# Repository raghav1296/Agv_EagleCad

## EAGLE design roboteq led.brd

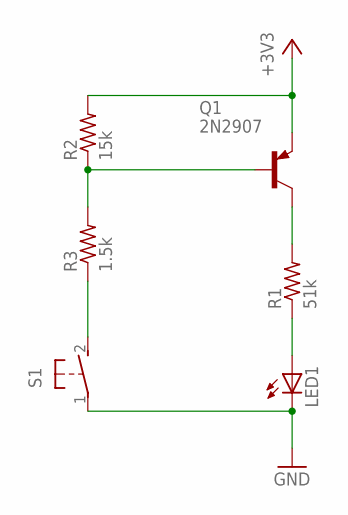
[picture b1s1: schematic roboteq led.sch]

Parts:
LED1: LED; SMARTLED-TTW
Q1: 2N2907; TO92-EBC-OVAL
R1: 51k; 0204V
R2: 15k; 0204V
R3: 1.5k; 0204V
S1: 31-XX; B3F-31XX

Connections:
+3V3: Q1.E, R2.2
GND: LED1.C@1 (C), S1.1
unnamed: Q1.C, R1.2
unnamed: LED1.A@1 (A), R1.1
unnamed: Q1.B, R2.1, R3.2
unnamed: R3.1, S1.2 (S)

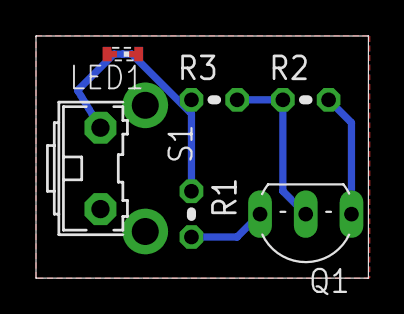
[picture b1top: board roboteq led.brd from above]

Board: 2 copper layers, 18.5 x 13.5 mm, 6 parts (0 on the bottom side), 6 nets.

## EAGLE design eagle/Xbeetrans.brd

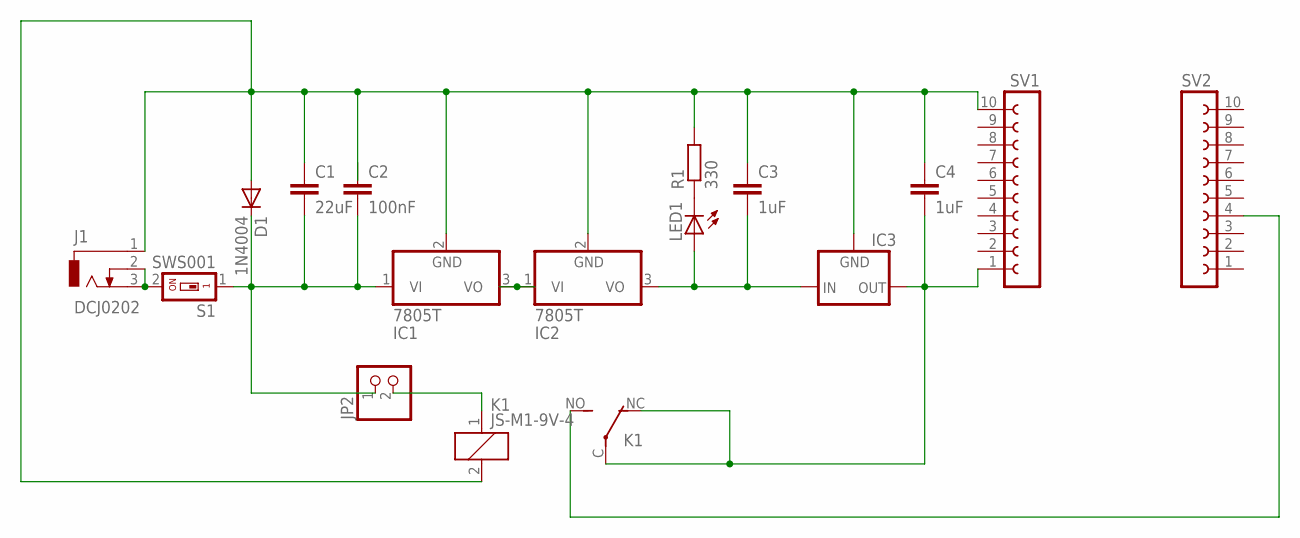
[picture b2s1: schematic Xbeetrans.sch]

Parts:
C1: 22uF; C025-025X050
C2: 100nF; C025-025X050
C3, C4: 1uF; C025-025X050
D1: 1N4004; DO41-10
IC1, IC2: 7805T; TO220H
IC3: MCP1700TRI; TO92
J1: DCJ0202
JP2: PINHD-1X2; 1X02
K1: JS-M1-9V-4; JS-M
LED1: LED3MM
R1: 330; 0204/5
S1: SWS001; SMS-001
SV1, SV2: FE10-1; FE10

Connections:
GND: C1.1, C2.1, C3.1, C4.1, D1.A, IC1.2 (GND), IC2.2 (GND), IC3.1 (GND), J1.1, K1.2, R1.2, SV1.10
unnamed: J1.2, J1.3, S1.2
unnamed: C1.2, C2.2, D1.C, IC1.1 (VI), JP2.1, S1.1
unnamed: JP2.2, K1.1
unnamed: LED1.K (C), R1.1
unnamed: C3.2, IC2.3 (VO), IC3.2 (IN), LED1.A
unnamed: IC1.3 (VO), IC2.1 (VI)
XBEE3.3: C4.2, IC3.3 (OUT), K1.C, K1.NC (O), SV1.1
XBEED: K1.NO (S), SV2.4

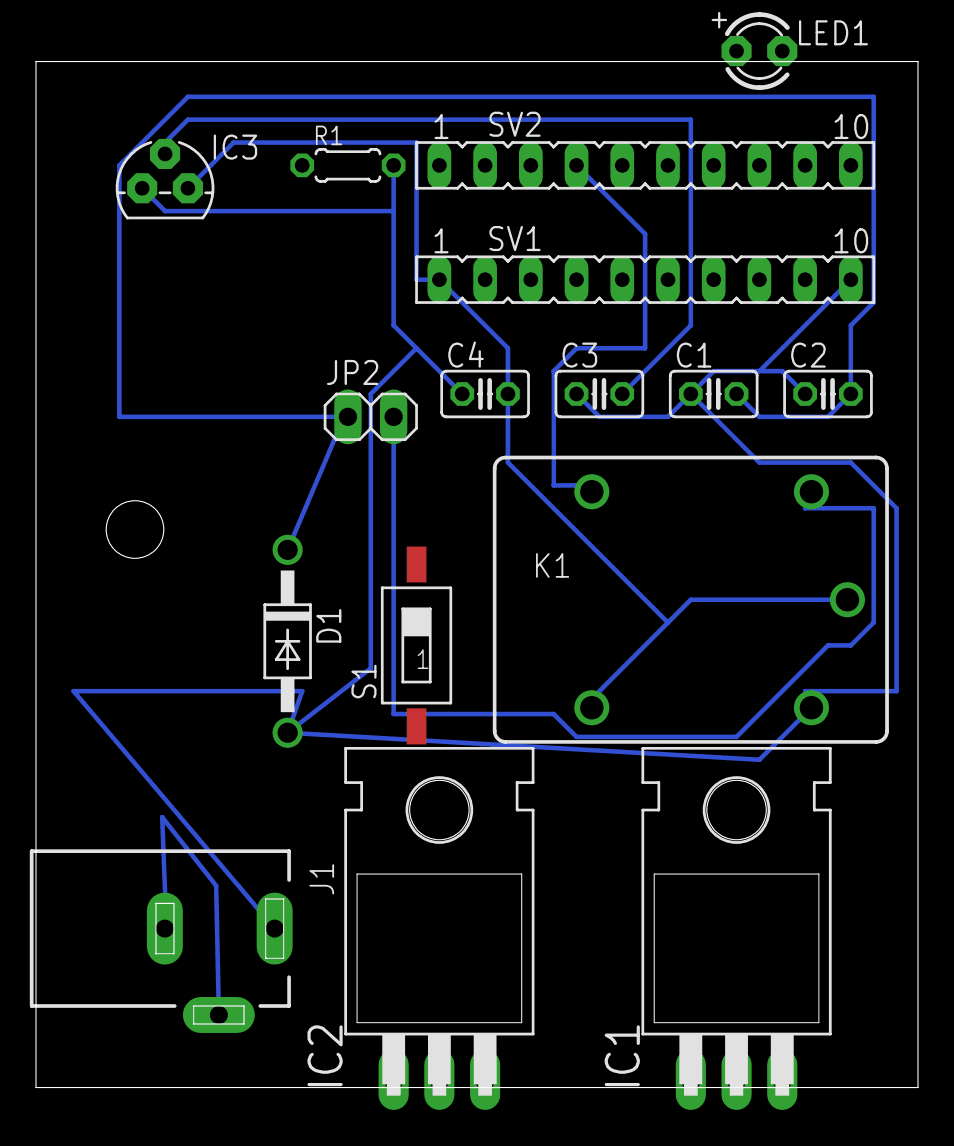
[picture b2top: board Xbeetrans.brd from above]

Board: 2 copper layers, 49.0 x 57.0 mm, 16 parts (0 on the bottom side), 9 nets.

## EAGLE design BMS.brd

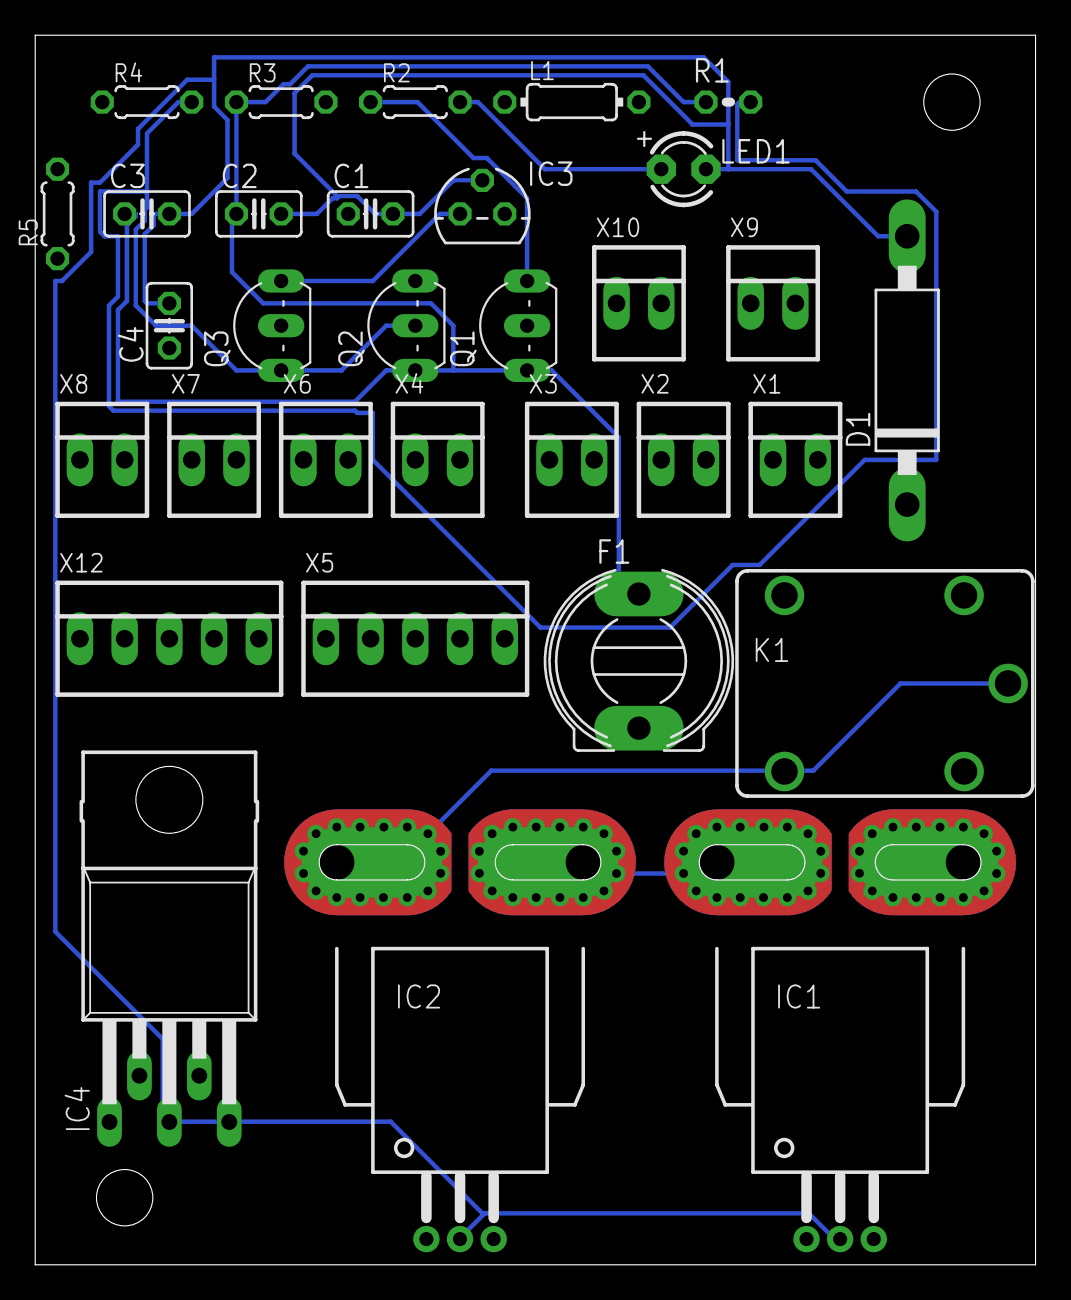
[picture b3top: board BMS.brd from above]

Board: 2 copper layers, 56.8 x 69.8 mm, 32 parts (0 on the bottom side), 13 nets.

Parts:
C1, C2, C3, C4: C025-025X050
D1: C1702-15
F1: KS9V
IC1, IC2: ACS750LCA-050; ACS75050
IC3: 78L08Z; TO92
IC4: TO220-52
K1: CQ1-12V; CQ1
L1: 0204/7
LED1: LED3MM
Q1, Q2, Q3: 2N2907; TO92-EBC-OVAL
R1: 0204V
R2, R3, R4, R5: 0204/5
X1, X2, X3, X4, X6, X7, X8, X9, X10: 22-23-2021
X5, X12: 22-23-2051

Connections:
+12V: IC1.IP-, IC1.IP-@2, IC1.IP-@3, IC1.IP-@4, IC1.IP-@5, IC1.IP-@6, IC1.IP-@7, IC1.IP-@8, IC1.IP-@9, IC1.IP-@10, IC1.IP-@11, IC1.IP-@12, IC1.IP-@13, IC1.IP-@14, IC1.IP-@15, IC1.IP-@16, IC1.IP-@17, IC2.IP+, IC2.IP+@2, IC2.IP+@3, IC2.IP+@4, IC2.IP+@5, IC2.IP+@6, IC2.IP+@7, IC2.IP+@8, IC2.IP+@9, IC2.IP+@10, IC2.IP+@11, IC2.IP+@12, IC2.IP+@13, IC2.IP+@14, IC2.IP+@15, IC2.IP+@16, IC2.IP+@17
GND: C1.2, C2.2, C3.2, C4.2, D1.A, IC1.2, IC2.2, IC3.2, IC4.3, IC4.5, K1.1, LED1.K
unnamed: C2.1, C3.1, F1.1, IC1.IP+, IC1.IP+@2, IC1.IP+@3, IC1.IP+@4, IC1.IP+@5, IC1.IP+@6, IC1.IP+@7, IC1.IP+@8, IC1.IP+@9, IC1.IP+@10, IC1.IP+@11, IC1.IP+@12, IC1.IP+@13, IC1.IP+@14, IC1.IP+@15, IC1.IP+@16, IC1.IP+@17, IC4.1, K1.NO, Q1.E, Q2.E, R1.1, R3.1
unnamed: IC2.IP-, IC2.IP-@2, IC2.IP-@3, IC2.IP-@4, IC2.IP-@5, IC2.IP-@6, IC2.IP-@7, IC2.IP-@8, IC2.IP-@9, IC2.IP-@10, IC2.IP-@11, IC2.IP-@12, IC2.IP-@13, IC2.IP-@14, IC2.IP-@15, IC2.IP-@16, IC2.IP-@17, K1.C, K1.NC
unnamed: C1.1, F1.2
unnamed: Q1.C, R2.1
unnamed: LED1.A, R2.2
unnamed: Q2.B, Q3.E, R1.2, R4.2
unnamed: Q2.C, Q3.B, R3.2, R5.1
unnamed: D1.C, IC4.2, L1.2
unnamed: C4.1, IC4.4, L1.1
unnamed: Q1.B, R4.1
unnamed: IC3.1, Q3.C

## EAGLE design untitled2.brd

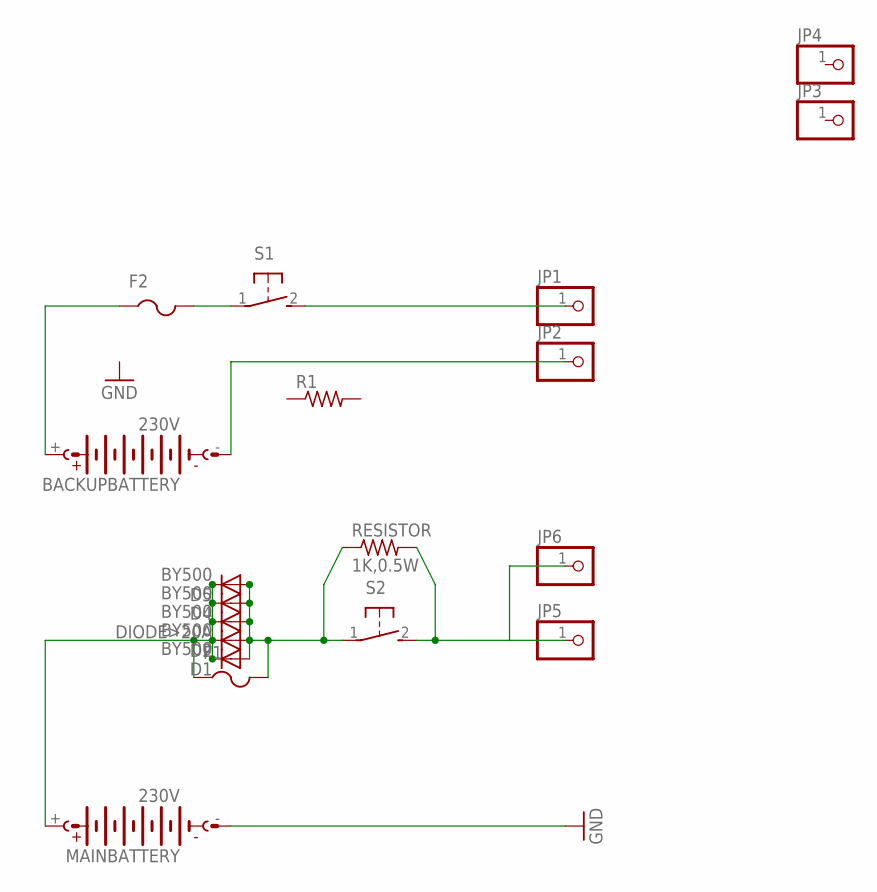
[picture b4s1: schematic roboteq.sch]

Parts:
BACKUPBATTERY: 230V; AB9V
D1, D2, D4, D5: BY500; DO201-15
DIODE>20A: BY500; DO201-15
F1, F2: PTCFUSE-1206; R1206
JP1, JP2, JP3, JP4, JP5, JP6: PINHD-1X1; 1X01
MAINBATTERY: 230V; AB9V
R1: R-US_0204/5; 0204/5
RESISTOR: 1K,0.5W; 0204/5
S1, S2: 31-XX; B3F-31XX

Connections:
.: D1.C, D2.C, D4.C, D5.C, DIODE>20A.C, F1.1, MAINBATTERY.+
GND: MAINBATTERY.-
unnamed: D1.A, D2.A, D4.A, D5.A, DIODE>20A.A, F1.2, RESISTOR.1, S2.1
unnamed: JP5.1, JP6.1, RESISTOR.2, S2.2 (S)
unnamed: BACKUPBATTERY.+, F2.1
unnamed: F2.2, S1.1
unnamed: JP1.1, S1.2 (S)
unnamed: BACKUPBATTERY.-, JP2.1

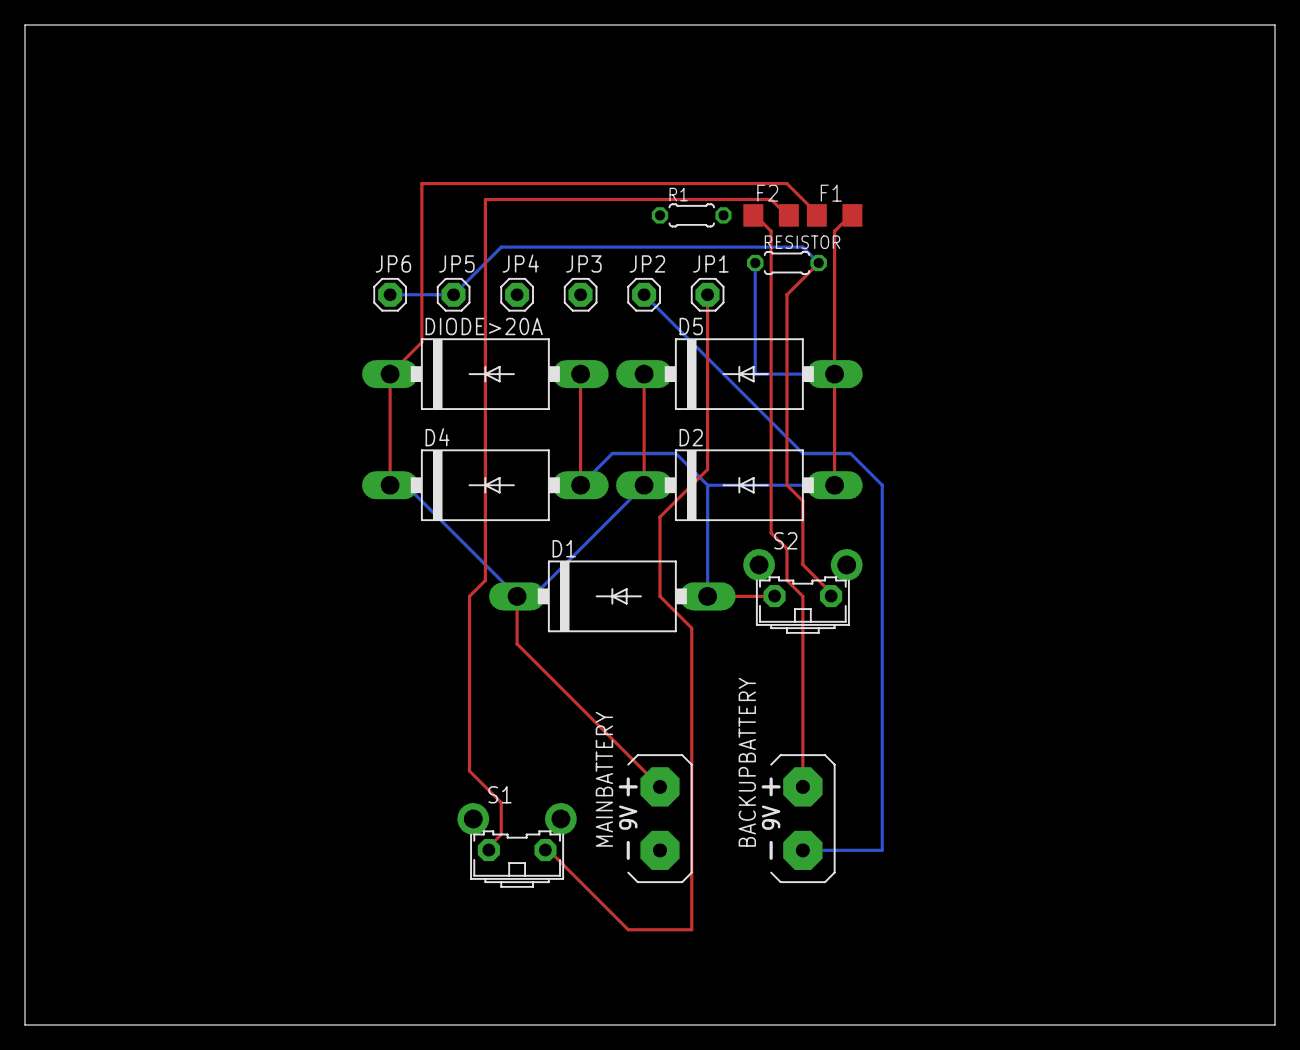
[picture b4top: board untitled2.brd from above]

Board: 2 copper layers, 100.0 x 80.0 mm, 19 parts (0 on the bottom side), 7 nets.

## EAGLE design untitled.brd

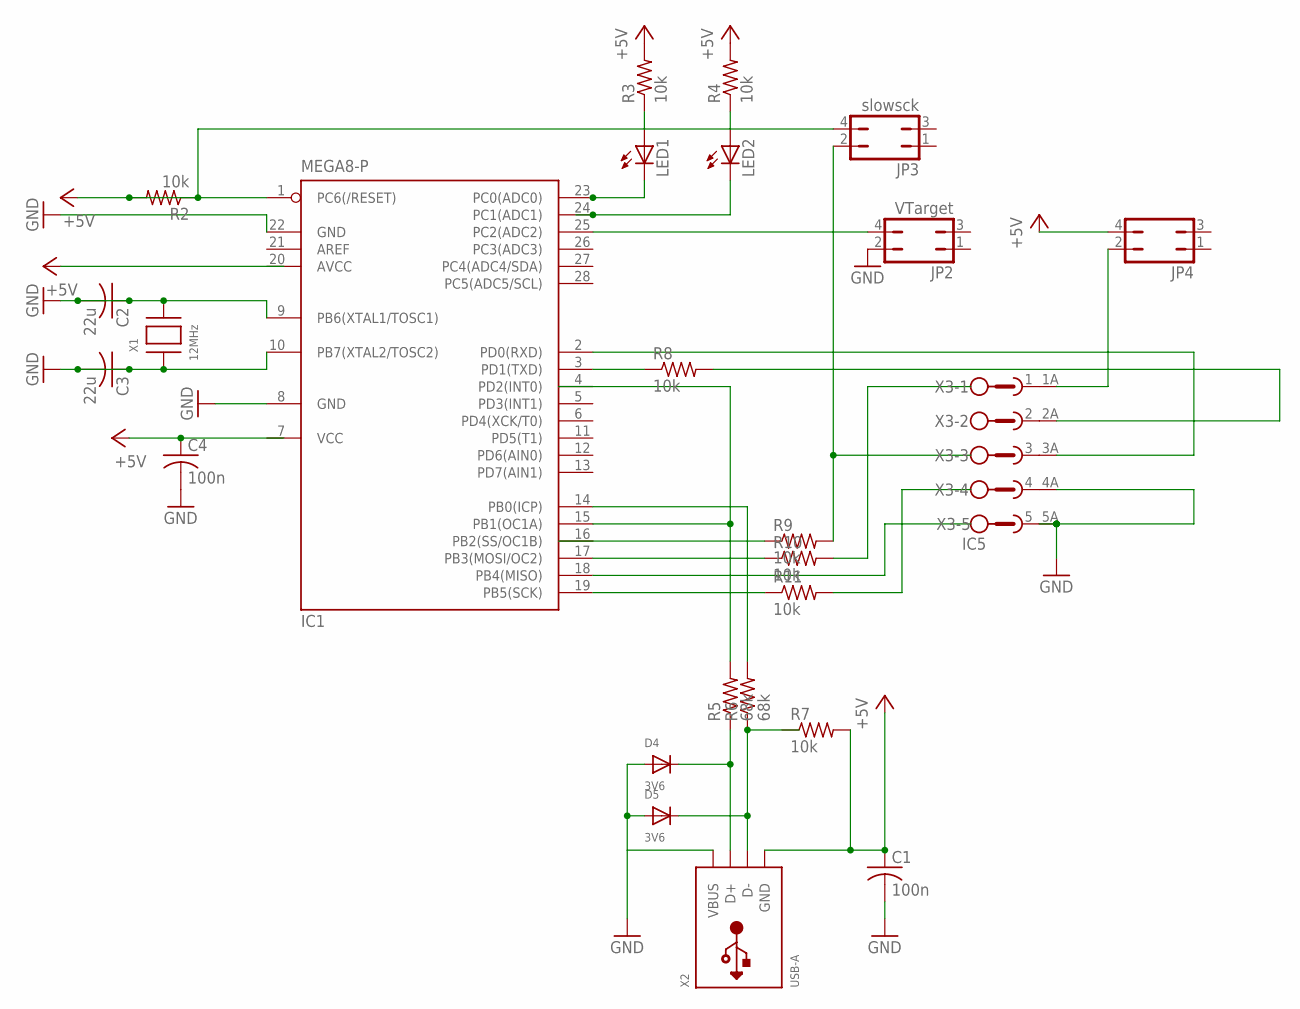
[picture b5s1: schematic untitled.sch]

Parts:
C1, C4: 100n; C025-024X044
C2, C3: 22u; C025-024X044
D4, D5: 3V6; DO-1N4148
IC1: MEGA8-P; DIL28-3
JP2: VTarget; JP2Q
JP3: slowsck; JP2Q
JP4: JP2Q
LED1, LED2: LED5MM
R2, R3, R4, R7, R8, R9, R10, R11: 10k; 0204V
R5, R6: 68k; 0204V
X1: 12MHz; XTAL3215
X2: USB-A; MOLEX_480371000
X3: IC5

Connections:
+5V: C1.1, C4.1, IC1.1 (PC6(/RESET)), JP3.4, JP4.4, R2.1, R2.2, R3.2, R4.2, R7.2, X2.4 (GND)
AVCC: IC1.20 (AVCC)
GND: C1.2, C2.1, C2.2, C3.1, C3.2, C4.2, D4.A, D5.A, IC1.8 (GND), IC1.9 (PB6(XTAL1/TOSC1)), IC1.10 (PB7(XTAL2/TOSC2)), IC1.22 (GND), JP2.2, X1.P$1, X1.P$2, X2.1 (VBUS)
unnamed: LED1.A, R3.1
unnamed: IC1.23 (PC0(ADC0)), LED1.K (C)
unnamed: IC1.24 (PC1(ADC1)), LED2.K (C)
unnamed: LED2.A, R4.1
unnamed: IC1.25 (PC2(ADC2)), JP2.4
unnamed: D4.C, R5.1, X2.3 (D+)
unnamed: D5.C, R6.1, X2.2 (D-)
unnamed: IC1.15 (PB1(OC1A)), R5.2
unnamed: IC1.14 (PB0(ICP)), R6.2
unnamed: JP3.2, R9.2
unnamed: IC1.17 (PB3(MOSI/OC2)), R10.1
unnamed: IC1.19 (PB5(SCK)), R11.1
unnamed: JP4.2, X3.1A (2)
unnamed: IC1.2 (PD0(RXD)), X3.3A (2)
unnamed: R8.2, X3.2A (2)
unnamed: IC1.3 (PD1(TXD)), R8.1
unnamed: X3.4A (2), X3.5 (1), X3.5A (2)
VCC: IC1.7 (VCC)

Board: 2 copper layers, 25 parts (0 on the bottom side), 19 nets, no tracks yet.

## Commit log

2015-03-22 usb asp
2015-03-22 Revert "usb asp"
    This reverts commit 9eb07d9146d0651e0feae7b3cc6f252f5dde46eb.
2015-03-22 Revert "Revert "usb asp""
    This reverts commit e0dea1e98b771a1e29ceddb097928f3be1333105.
2015-03-29 MYSTMARMZ
2015-03-29 Revert "MYSTMARMZ"
    This reverts commit 574e46aa263eab85cf76c740bb46a0becdb3f195.
2015-03-29 eagle schematics and board
2015-03-29 coocox
2015-03-29 eagle
2015-04-03 flash led roboteq
2015-04-29 itch
2015-09-29 L293d.png
